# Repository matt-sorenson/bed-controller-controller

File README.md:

# bed-controller-controller

This controls a Richmat HJH89 remote control that came with my bed but should work for any remote.

It has 3 memory buttons that are controlled by the ESP32-C6 controller (zg (zero-g), sit-up (memory) & flat)

I didn't include the massage buttons, underbed light, lumbar or head tilt as I never used them.

The switchs controlling the Head Up/Down & Feet Up/Down are not controllable from the ESP as the delay made it hard to actually get it to a possition you want.

## Parts List

1x [Bed Remote](https://svenandson.com/products/sven-son-replacement-remote?variant=32488578908238)
3x [Relays](https://www.digikey.com/en/products/detail/te-connectivity-potter-brumfield-relays/1462041-7/2126941)
3x [Transistors](https://www.digikey.com/en/products/detail/diodes-incorporated/MMBT3904-7-F/814494)
1x [Seeed Studio XIAO ESP32-C6](https://www.seeedstudio.com/Seeed-Studio-XIAO-ESP32C6-p-5884.html)
7x Cherry-MX Keyswitches
7x relegendable keycaps (the ones pictures were random purchase from amazon, trying laser engraving blank black keycaps when I can)
1x 2-pin picoblade inline male (power cable)
1x 2-pin picoblade inline female (power cable)
1x 6-pin picoblade inline male
1x 6-pin picoblade inline female
1x 8-pin picoblade inline male
1x 8-pin picoblade inline female

### Notes

- it doesn't matter which set of pins are connected with the 6 or 8 pin, just make sure you wire them to the correct contacts on the OEM remote.
- For my OEM Remote PCB I rounded the corners of the PCB with sandpaper, needed within the provided case but no real functional reason.

## Pictures along the way

Board with all parts soldered on.

### Top of board with components soldered in place

### Bottom of board with components & wires soldered in place along with OEM remote

### PCBs placed inside the case

The foam block is a cube from [this sheet](https://www.mcmaster.com/catalog/131/4104/3157T23). It keeps the OEM PCB in place as there's no good place to put a screw through that PCB.

### Completed Assembly

Don't know how I got so lucky on the clearances but my print of the case stays together well but is easy enough to take back apart.

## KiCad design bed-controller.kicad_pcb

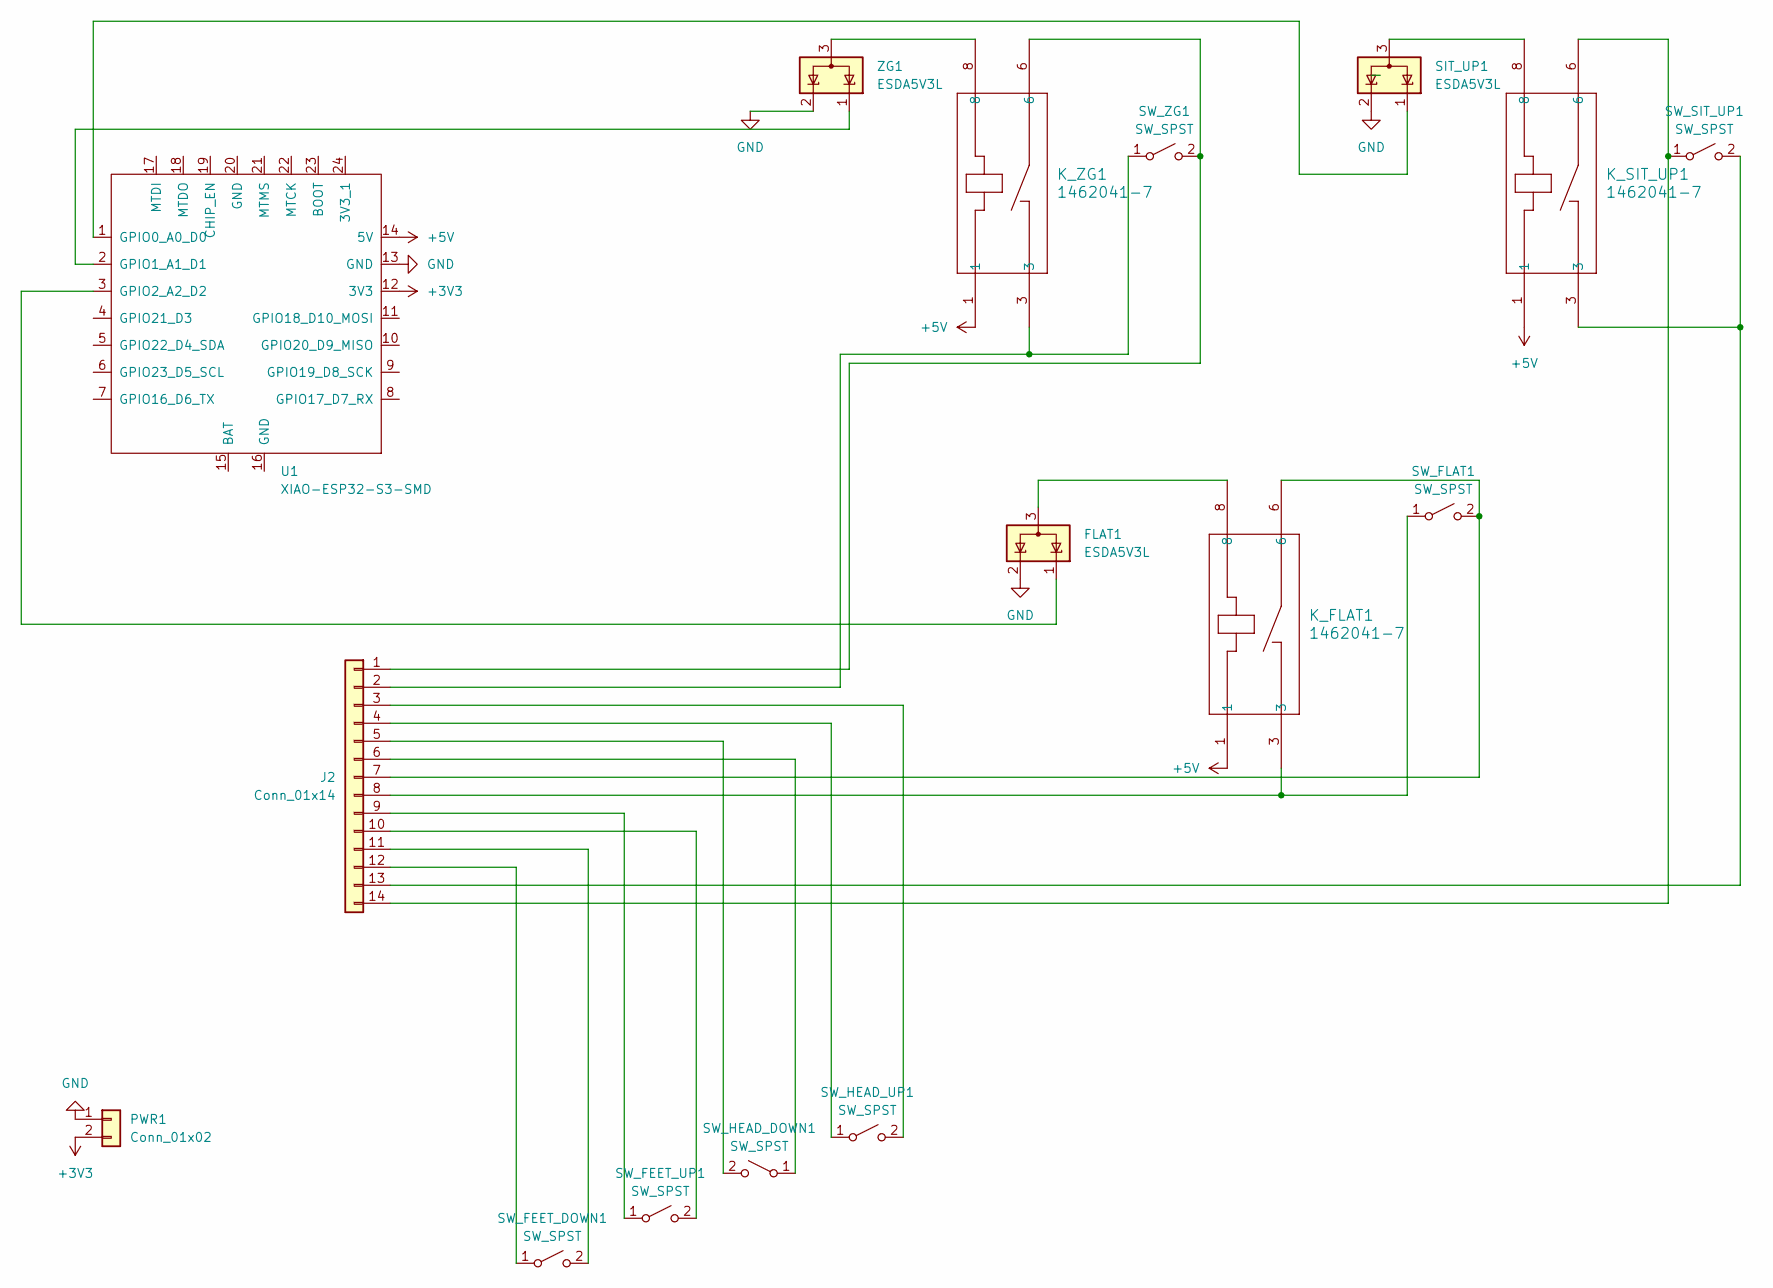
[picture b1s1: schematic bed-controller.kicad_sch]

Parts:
FLAT1: ESDA5V3L; SOT-23-3
J2: Conn_01x14; PinHeader_1x14_P2.54mm_Vertical
K_FLAT1: 1462041-7; bigger-pads-RELAY4_1462041-7_TEC
K_SIT_UP1: 1462041-7; bigger-pads-RELAY4_1462041-7_TEC
K_ZG1: 1462041-7; bigger-pads-RELAY4_1462041-7_TEC
PWR1: Conn_01x02; PinHeader_1x02_P2.54mm_Vertical
SIT_UP1: ESDA5V3L; SOT-23-3
SW_FEET_DOWN1: SW_SPST; center-SW_Cherry_MX_1.00u_PCB
SW_FEET_UP1: SW_SPST; center-SW_Cherry_MX_1.00u_PCB
SW_FLAT1: SW_SPST; center-SW_Cherry_MX_1.00u_PCB
SW_HEAD_DOWN1: SW_SPST; center-SW_Cherry_MX_1.00u_PCB
SW_HEAD_UP1: SW_SPST; center-SW_Cherry_MX_1.00u_PCB
SW_SIT_UP1: SW_SPST; center-SW_Cherry_MX_1.00u_PCB
SW_ZG1: SW_SPST; center-SW_Cherry_MX_1.00u_PCB
U1: XIAO-ESP32-S3-SMD; XIAO-ESP32C6-SMD-bigger-pads
ZG1: ESDA5V3L; SOT-23-3

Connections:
+3V3: PWR1.2, U1.12 (3V3)
+5V: K_FLAT1.1, K_SIT_UP1.1, K_ZG1.1, U1.14 (5V)
GND: FLAT1.2 (K), PWR1.1, SIT_UP1.2 (K), U1.13 (GND), ZG1.2 (K)
unnamed: FLAT1.3 (A), K_FLAT1.8
unnamed: J2.1, K_ZG1.6, SW_ZG1.2 (B)
unnamed: J2.2, K_ZG1.3, SW_ZG1.1 (A)
unnamed: J2.3, SW_HEAD_UP1.2 (B)
unnamed: J2.4, SW_HEAD_UP1.1 (A)
unnamed: J2.5, SW_HEAD_DOWN1.2 (B)
unnamed: J2.6, SW_HEAD_DOWN1.1 (A)
unnamed: J2.7, K_FLAT1.6, SW_FLAT1.2 (B)
unnamed: J2.8, K_FLAT1.3, SW_FLAT1.1 (A)
unnamed: J2.9, SW_FEET_UP1.1 (A)
unnamed: J2.10, SW_FEET_UP1.2 (B)
unnamed: J2.11, SW_FEET_DOWN1.2 (B)
unnamed: J2.12, SW_FEET_DOWN1.1 (A)
unnamed: J2.13, K_SIT_UP1.3, SW_SIT_UP1.2 (B)
unnamed: J2.14, K_SIT_UP1.6, SW_SIT_UP1.1 (A)
unnamed: K_SIT_UP1.8, SIT_UP1.3 (A)
unnamed: SIT_UP1.1 (K), U1.1 (GPIO0_A0_D0)
unnamed: U1.2 (GPIO1_A1_D1), ZG1.1 (K)
unnamed: FLAT1.1 (K), U1.3 (GPIO2_A2_D2)
unnamed: K_ZG1.8, ZG1.3 (A)

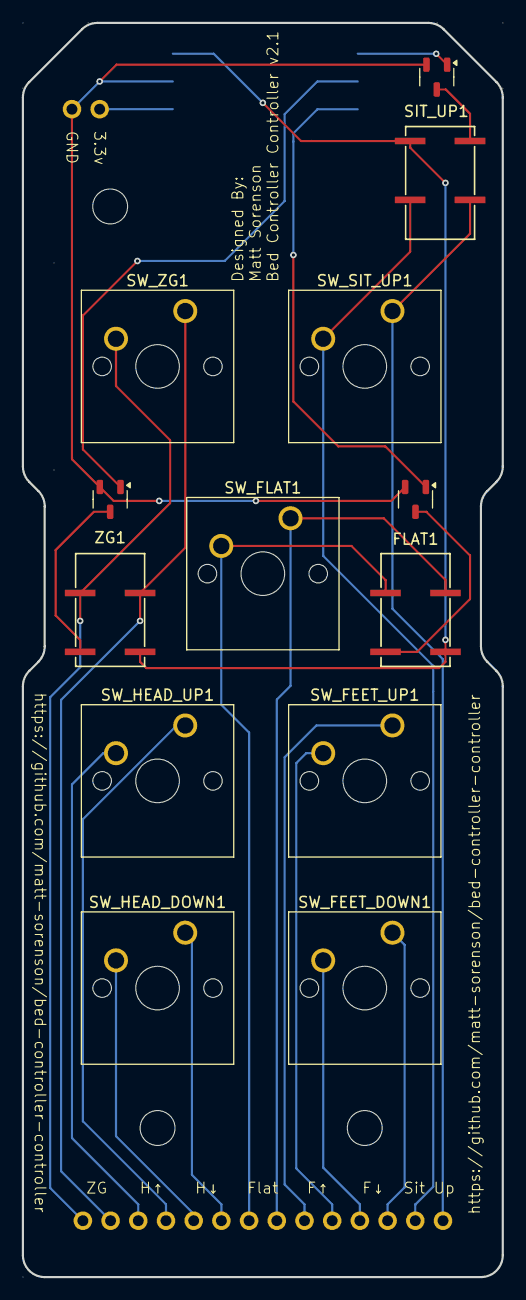
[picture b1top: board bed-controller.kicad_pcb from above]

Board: 2 copper layers, 44.0 x 115.0 mm, 16 parts (1 on the bottom side), 23 nets.

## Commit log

2025-02-28 v1 gerber files
2025-02-28 v2 gerber files
2025-02-28 v2.1 kicad project & gerber files
2025-02-28 remove gerber files
2025-02-28 3mf file to hold PCB & the OEM board from bed.
2025-02-28 readme & images
2025-03-02 add key labels svg file
